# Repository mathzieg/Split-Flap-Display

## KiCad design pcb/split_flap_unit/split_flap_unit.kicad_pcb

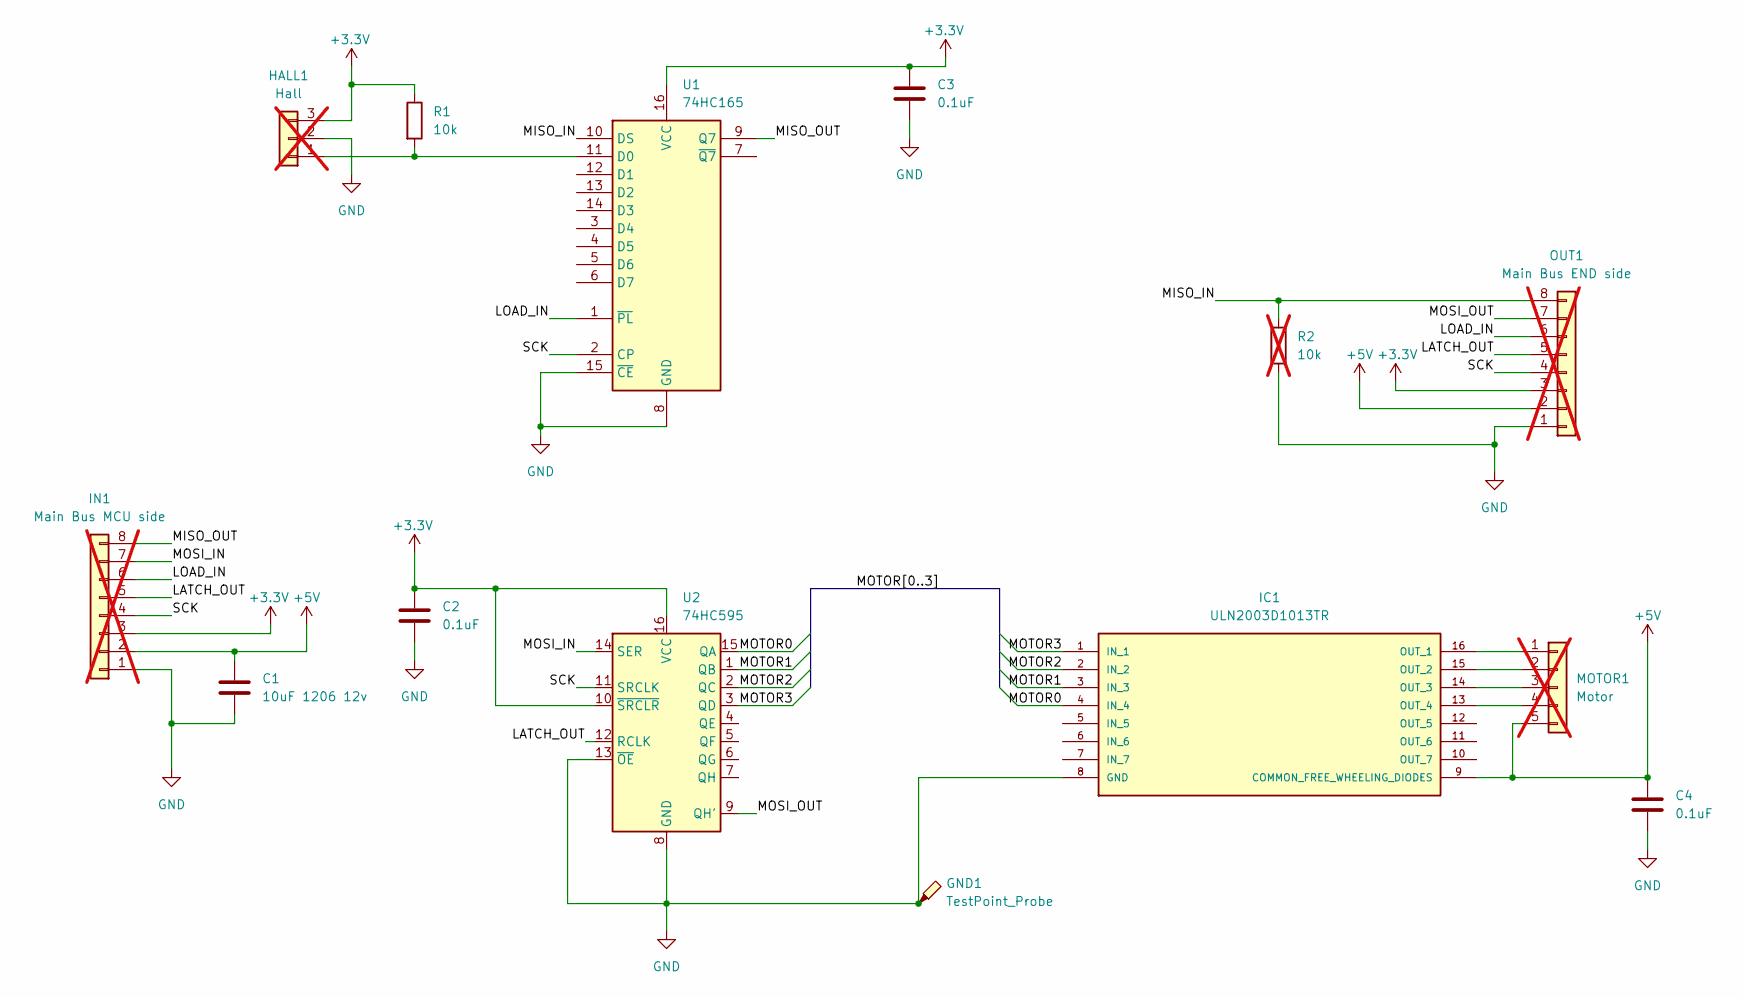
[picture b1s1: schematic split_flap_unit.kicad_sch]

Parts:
C1: 10uF 1206 12v; C_1206_3216Metric_Pad1.33x1.80mm_HandSolder
C2, C3, C4: 0.1uF; C_0805_2012Metric_Pad1.18x1.45mm_HandSolder
GND1: TestPoint_Probe; TestPoint_Pad_D2.0mm
HALL1: Hall; JST_XH_B3B-XH-AM_1x03_P2.50mm_Vertical; not fitted
IC1: ULN2003D1013TR; SOIC-16_3.9x9.9mm_P1.27mm; MOUSER_PART_NUMBER 511-ULN2003D1013TR
IN1: Main Bus MCU side; PinHeader_1x08_P2.54mm_Horizontal; not fitted
MOTOR1: Motor; JST_XH_B5B-XH-AM_1x05_P2.50mm_Vertical; not fitted
OUT1: Main Bus END side; PinSocket_1x08_P2.54mm_Horizontal; not fitted
R1: 10k; R_0805_2012Metric_Pad1.20x1.40mm_HandSolder
R2: 10k; R_0805_2012Metric_Pad1.20x1.40mm_HandSolder; not fitted
U1: 74HC165; SOIC-16_3.9x9.9mm_P1.27mm
U2: 74HC595; SOIC-16_3.9x9.9mm_P1.27mm

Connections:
+3.3V: C2.1, C3.1, HALL1.3, IN1.3, OUT1.3, R1.1, U1.16 (VCC), U2.10 (~SRCLR), U2.16 (VCC)
+5V: C1.1, C4.1, IC1.9 (COMMON_FREE_WHEELING_DIODES), IN1.2, MOTOR1.5, OUT1.2
/LATCH_OUT: IN1.5, OUT1.5, U2.12 (RCLK)
/LOAD_IN: IN1.6, OUT1.6, U1.1 (~PL)
/MISO_IN: OUT1.8, R2.1, U1.10 (DS)
/MISO_OUT: IN1.8, U1.9 (Q7)
/MOSI_IN: IN1.7, U2.14 (SER)
/MOSI_OUT: OUT1.7, U2.9 (QH')
/MOTOR0: IC1.4 (IN_4), U2.15 (QA)
/MOTOR1: IC1.3 (IN_3), U2.1 (QB)
/MOTOR2: IC1.2 (IN_2), U2.2 (QC)
/MOTOR3: IC1.1 (IN_1), U2.3 (QD)
/SCK: IN1.4, OUT1.4, U1.2 (CP), U2.11 (SRCLK)
GND: C1.2, C2.2, C3.2, C4.2, GND1.1 (1_1), HALL1.2, IC1.8 (GND), IN1.1, OUT1.1, R2.2, U1.8 (GND), U1.15 (~CE), U2.8 (GND), U2.13 (~OE)
unnamed: HALL1.1, R1.2, U1.11 (D0)
unnamed: IC1.16 (OUT_1), MOTOR1.1
unnamed: IC1.15 (OUT_2), MOTOR1.2
unnamed: IC1.14 (OUT_3), MOTOR1.3
unnamed: IC1.13 (OUT_4), MOTOR1.4

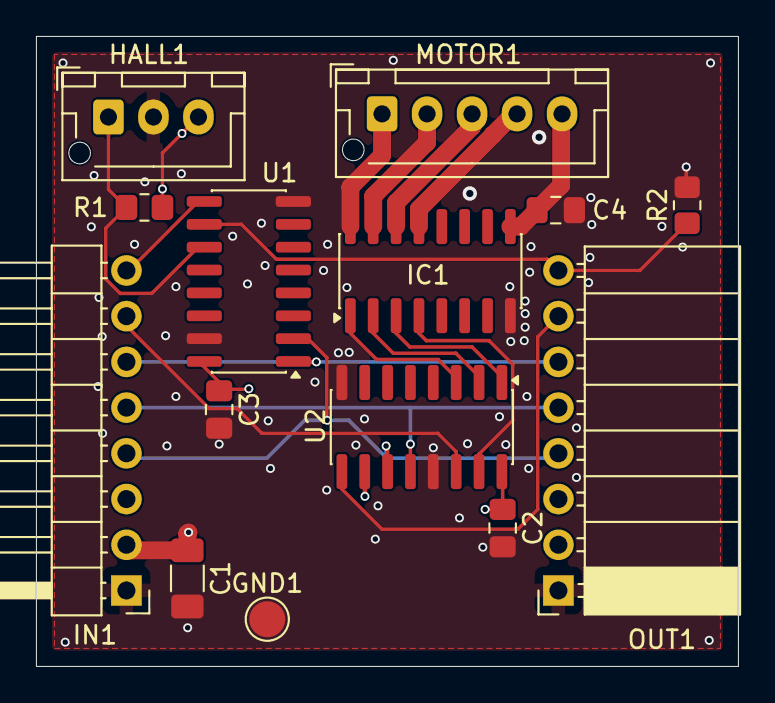
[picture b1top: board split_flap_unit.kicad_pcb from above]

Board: 4 copper layers, 39.0 x 35.0 mm, 14 parts (0 on the bottom side), 19 nets.

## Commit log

2026-04-08 updated for spi
2026-04-10 Changed spi pin
2026-04-13 added the pcbs
2026-04-30 added thermal relief on main pcb and corrected an error
2026-04-30 Added text on pcb
